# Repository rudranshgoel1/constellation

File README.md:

# constellation

### what is it
> it is a constellation pcb of "sagittarius", it includes 21 leds and a coin cell for powering them. it lights up and shows the constellation.

### BOM
|Name                |Quantity|Price (USD)|Link                                                                        |
|--------------------|--------|-----------|----------------------------------------------------------------------------|
|LEDs                |21      |0          |SELF SOURCED                                                                |
|Coin Cell           |1       |0          |SELF SOURCED                                                                |
|Coin Cell Holder SMD|1       |0.52       |https://www.digikey.com/en/products/detail/keystone-electronics/3034/4499289|
|PCB                 |5       |9.38       |https://jlcpcb.com/                                                         |
|                    |        |           |                                                                            |
|                    |        |9.9        |                                                                            |

Final cost is around $9.9

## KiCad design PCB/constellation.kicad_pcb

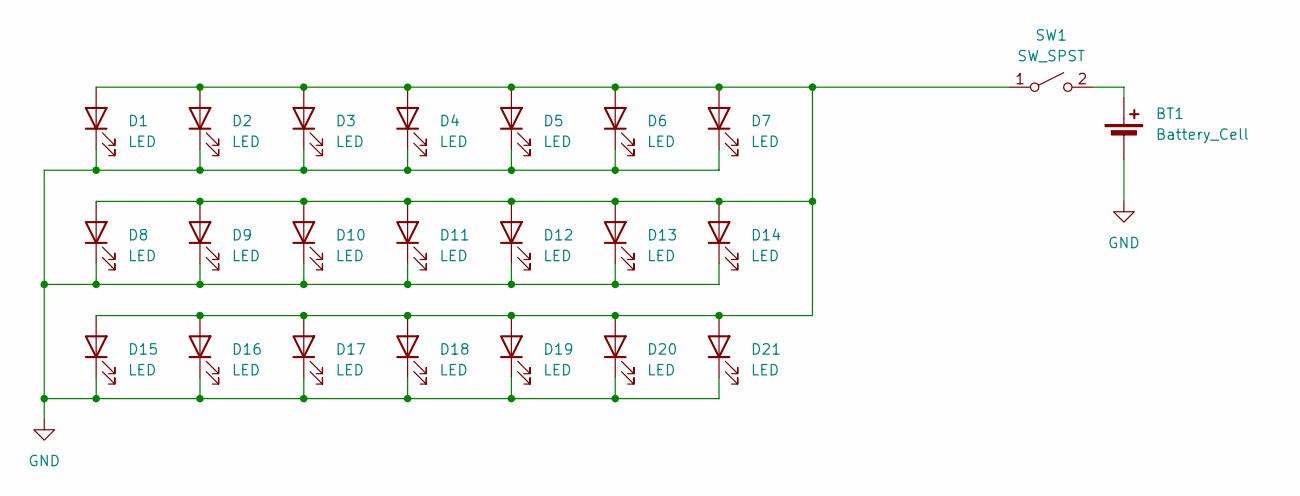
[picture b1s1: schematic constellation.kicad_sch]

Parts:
BT1: Battery_Cell; BatteryHolder_Keystone_3034_1x20mm
D1, D2, D3, D4, D5, D6, D7, D8, D9, D10, D11, D12, D13, D14, D15, D16, D17, D18, D19, D20, D21: LED; LED_D5.0mm
SW1: SW_SPST; SW_DIP_SPSTx01_Slide_9.78x4.72mm_W7.62mm_P2.54mm

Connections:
GND: BT1.2 (-), D1.1 (K), D2.1 (K), D3.1 (K), D4.1 (K), D5.1 (K), D6.1 (K), D7.1 (K), D8.1 (K), D9.1 (K), D10.1 (K), D11.1 (K), D12.1 (K), D13.1 (K), D14.1 (K), D15.1 (K), D16.1 (K), D17.1 (K), D18.1 (K), D19.1 (K), D20.1 (K), D21.1 (K)
unnamed: BT1.1 (+), SW1.2 (B)
unnamed: D1.2 (A), D2.2 (A), D3.2 (A), D4.2 (A), D5.2 (A), D6.2 (A), D7.2 (A), D8.2 (A), D9.2 (A), D10.2 (A), D11.2 (A), D12.2 (A), D13.2 (A), D14.2 (A), D15.2 (A), D16.2 (A), D17.2 (A), D18.2 (A), D19.2 (A), D20.2 (A), D21.2 (A), SW1.1 (A)

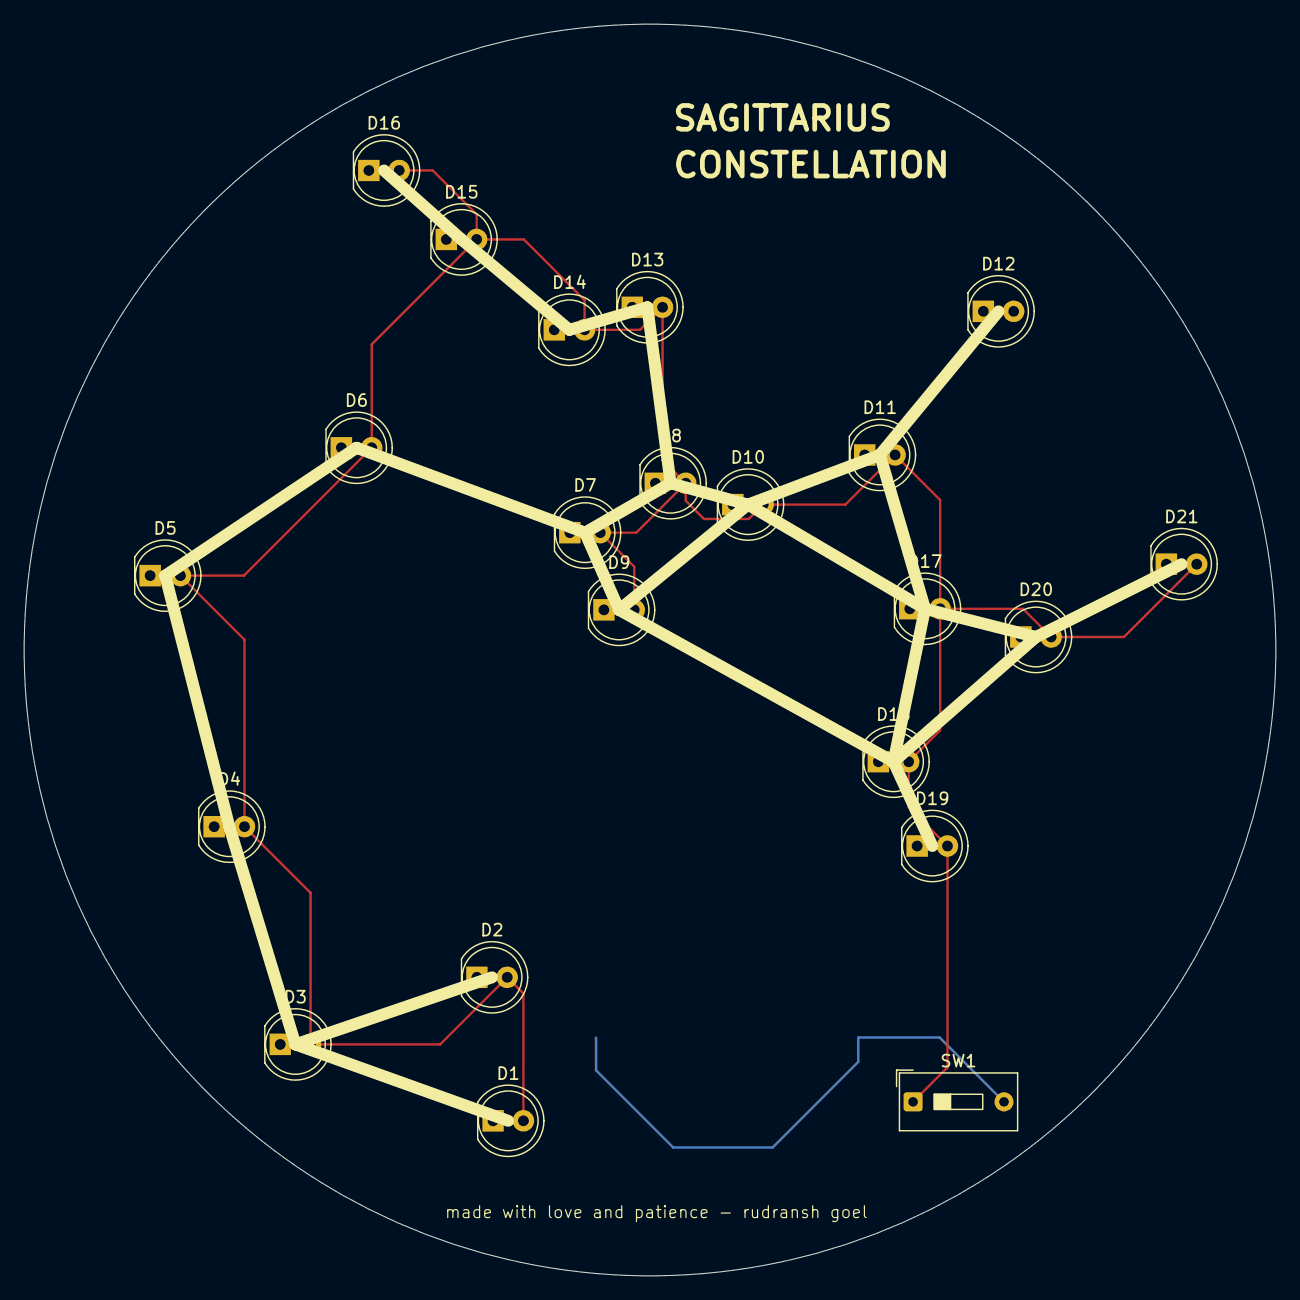
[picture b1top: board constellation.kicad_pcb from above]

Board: 2 copper layers, 104.8 x 104.8 mm, 23 parts (1 on the bottom side), 3 nets.
